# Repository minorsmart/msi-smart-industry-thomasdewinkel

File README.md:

# Open de [Wiki link](https://github.com/minorsmart/msi-smart-industry-thomasdewinkel/wiki) om bij mijn werk te komen

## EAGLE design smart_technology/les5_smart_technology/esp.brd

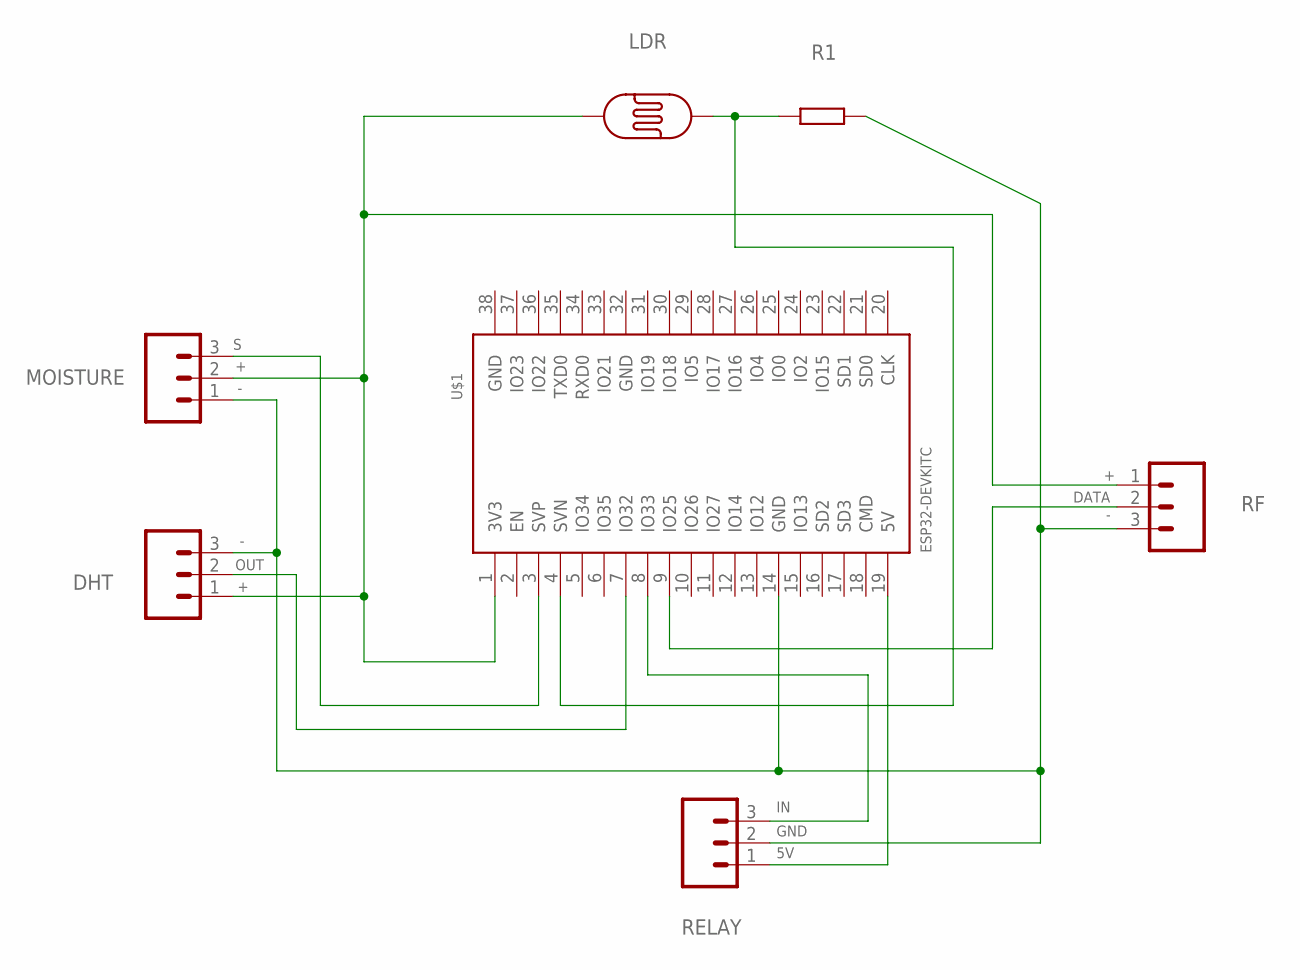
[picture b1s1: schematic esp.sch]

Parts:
DHT: 455-1750-1-ND; 1X03
LDR: PHOTOCELLPTH; PHOTOCELL
MOISTURE: 455-1750-1-ND; 1X03
R1: R-EU_0207/10; 0207/10
RELAY: 455-1750-1-ND; 1X03
RF: 455-1750-1-ND; 1X03
U$1: ESP32DEVKITC; ESP32-DEVKITC

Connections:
unnamed: DHT.1, LDR.1, MOISTURE.2, RF.1, U$1.1 (3V3)
unnamed: LDR.2, R1.1, U$1.4 (SVN)
unnamed: DHT.3, MOISTURE.1, R1.2, RELAY.2, RF.3, U$1.14 (GND)
unnamed: MOISTURE.3, U$1.3 (SVP)
unnamed: DHT.2, U$1.7 (IO32)
unnamed: RELAY.1, U$1.19 (5V)
unnamed: RELAY.3, U$1.8 (IO33)
unnamed: RF.2, U$1.9 (IO25)

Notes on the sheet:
OUT
GND
DATA

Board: 2 copper layers, 8 parts (0 on the bottom side), 8 nets, no tracks yet.

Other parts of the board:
U$2: RELAY

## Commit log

2021-09-02 Add online IDE url
2021-09-02 Repl.it Settings
2021-09-02 GitHub Classroom Feedback
2021-09-02 Setting up GitHub Classroom Feedback
2022-01-14 all files

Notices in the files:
parts and their libraries:
SparkFun-Connectors: Licensing: Creative Commons ShareAlike 4.0 International - https://creativecommons.org/licenses/by-sa/4.0
